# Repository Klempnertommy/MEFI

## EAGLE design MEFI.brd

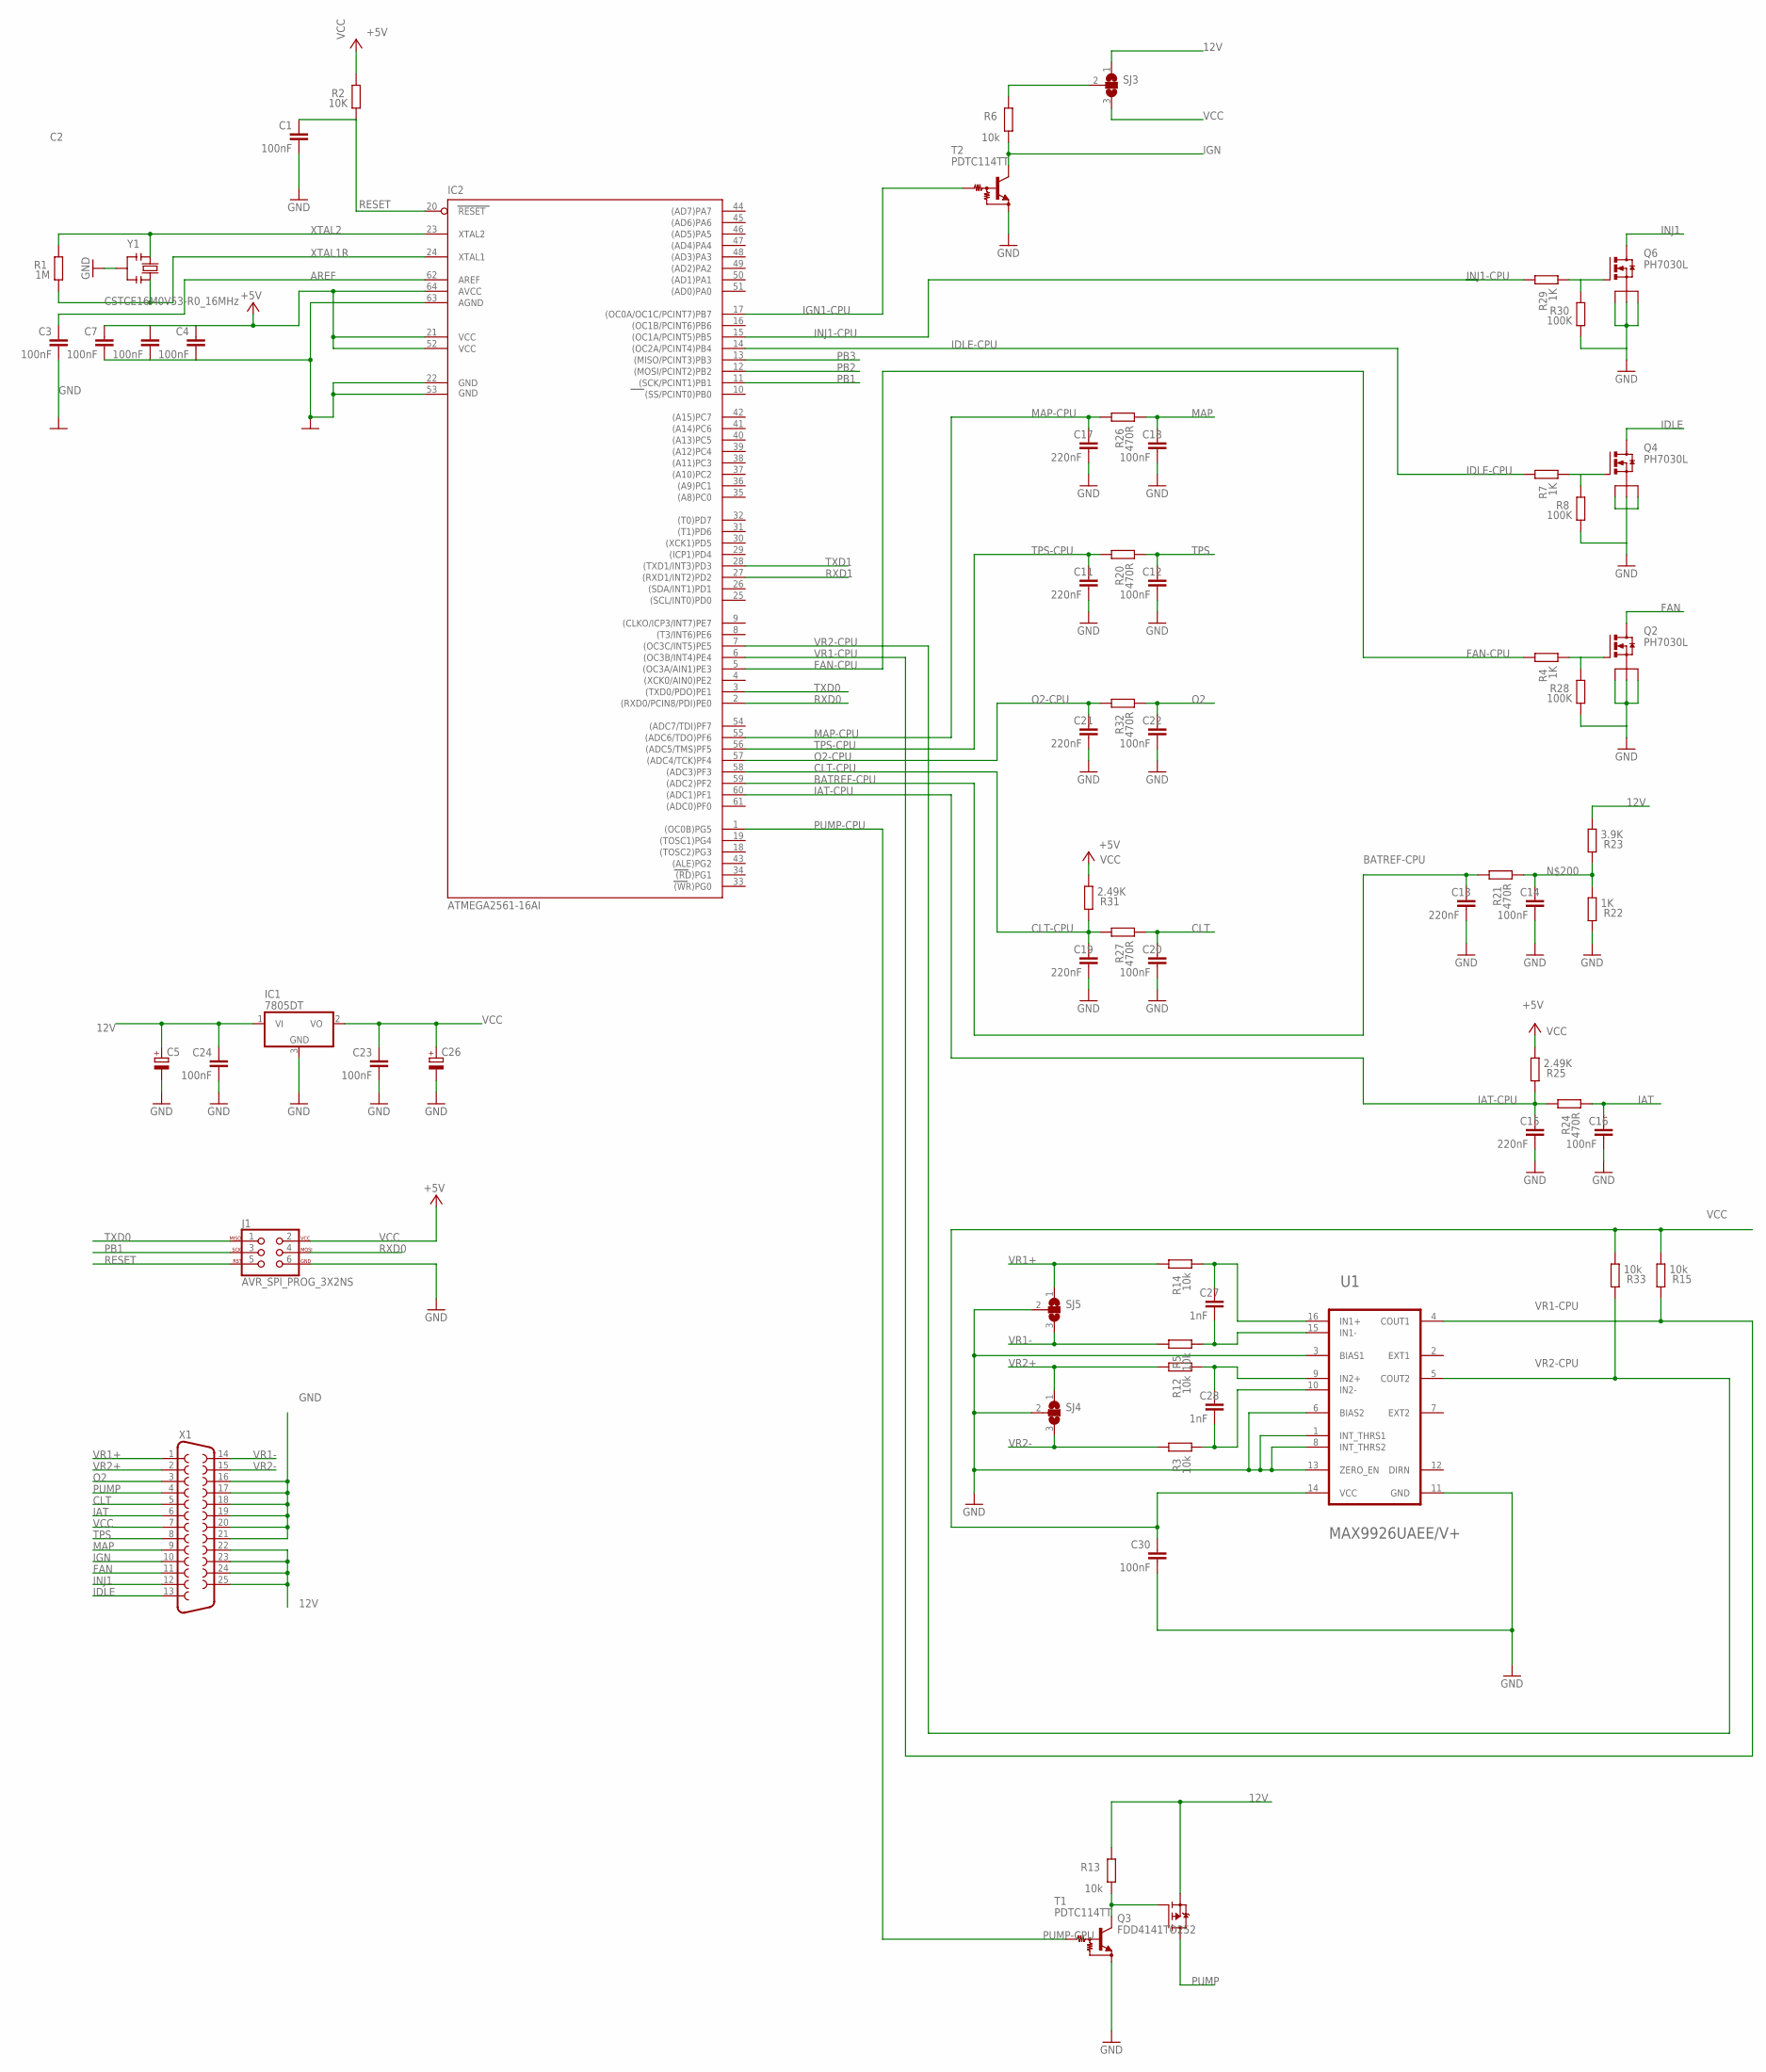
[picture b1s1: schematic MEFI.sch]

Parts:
C1, C2, C3, C4, C7, C12, C14, C16, C18, C20, C22, C23, C24, C30: 100nF; C0805
C5, C26: CPOL-EUTT2D7L; TT2D7L
C11, C13, C15, C17, C19, C21: 220nF; C0805
C27, C28: 1nF; C0805
IC1: 7805DT; TO252
IC2: ATMEGA2561-16AI; TQFP64
J1: AVR_SPI_PROG_3X2NS; 2X3-NS
Q2, Q4, Q6: PH7030L; SOT669
Q3: FDD4141TO252; TO252
R1: 1M; R0805
R2: 10K; R0805
R3, R5, R6, R12, R13, R14, R15, R33: 10k; R0805
R4, R7, R22, R29: 1K; R0805
R8, R28, R30: 100K; R0805
R20, R21, R24, R26, R27, R32: 470R; R0805
R23: 3.9K; R0805
R25, R31: 2.49K; R0805
SJ3, SJ4, SJ5: SJ2W; SJ_2
T1, T2: PDTC114TT; SC59-BEC
U1: MAXIM_MAX9926UAEE-V+MAXIM_MAX9926UAEE-V+_0_0; MAXIM_MAX9926UAEE-V+_0
X1: F25D
Y1: CSTCE16M0V53-R0_16MHz; RESONATOR

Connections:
12V: C5.+, C24.1, IC1.1 (VI), Q3.2 (S), R13.2, R23.1, SJ3.1, X1.22, X1.23, X1.24, X1.25
AREF: C3.1, IC2.62 (AREF)
BATREF-CPU: C13.1, IC2.59 ((ADC2)PF2), R21.2
CLT: C20.1, R27.1, X1.5
CLT-CPU: C19.1, IC2.58 ((ADC3)PF3), R27.2, R31.2
FAN: Q2.MB (D), X1.11
FAN-CPU: IC2.5 ((OC3A/AIN1)PE3), R4.2
GND: C1.2, C2.2, C3.2, C4.2, C5.-, C7.2, C11.2, C12.2, C13.2, C14.2, C15.2, C16.2, C17.2, C18.2, C19.2, C20.2, C21.2, C22.2, C23.2, C24.2, C26.-, C30.2, IC1.3 (GND), IC2.22 (GND), IC2.53 (GND1), IC2.63 (AGND), J1.6, Q2.1 (S), Q2.2 (S), Q2.3 (S), Q4.1 (S), Q4.2 (S), Q4.3 (S), Q6.1 (S), Q6.2 (S), Q6.3 (S), R8.1, R22.2, R28.1, R30.1, SJ4.2, SJ5.2, T1.E, T2.E, U1.1 (INT_THRS1), U1.3 (BIAS1), U1.6 (BIAS2), U1.8 (INT_THRS2), U1.11 (GND), U1.13 (ZERO_EN), X1.16, X1.17, X1.18, X1.19, X1.20, X1.21, Y1.2
IAT: C16.1, R24.1, X1.6
IAT-CPU: C15.1, IC2.60 ((ADC1)PF1), R24.2, R25.2
IDLE: Q4.MB (D), X1.13
IDLE-CPU: IC2.14 ((OC2A/PCINT4)PB4), R7.2
IGN: R6.1, T2.C, X1.10
IGN1-CPU: IC2.17 ((OC0A/OC1C/PCINT7)PB7), T2.B
INJ1: Q6.MB (D), X1.12
INJ1-CPU: IC2.15 ((OC1A/PCINT5)PB5), R29.2
MAP: C18.1, R26.1, X1.9
MAP-CPU: C17.1, IC2.55 ((ADC6/TDO)PF6), R26.2
unnamed: Q2.4 (G), R4.1, R28.2
unnamed: Q6.4 (G), R29.1, R30.2
unnamed: C28.2, R3.1, U1.10 (IN2-)
unnamed: C27.2, R5.1, U1.15 (IN1-)
unnamed: R6.2, SJ3.2
unnamed: Q3.1 (G), R13.1, T1.C
unnamed: C27.1, R14.1, U1.16 (IN1+)
unnamed: C28.1, R12.1, U1.9 (IN2+)
unnamed: Q4.4 (G), R7.1, R8.2
unnamed: C14.1, R21.1, R22.1, R23.2
O2: C22.1, R32.1, X1.3
O2-CPU: C21.1, IC2.57 ((ADC4/TCK)PF4), R32.2
PB1: IC2.11 ((SCK/PCINT1)PB1), J1.3
PB2: IC2.12 ((MOSI/PCINT2)PB2)
PB3: IC2.13 ((MISO/PCINT3)PB3)
PUMP: Q3.3 (D), X1.4
PUMP-CPU: IC2.1 ((OC0B)PG5), T1.B
RESET: C1.1, IC2.20 (RESET), J1.5, R2.1
RXD0: IC2.2 ((RXD0/PCIN8/PDI)PE0), J1.4
RXD1: IC2.27 ((RXD1/INT2)PD2)
TPS: C12.1, R20.1, X1.8
TPS-CPU: C11.1, IC2.56 ((ADC5/TMS)PF5), R20.2
TXD0: IC2.3 ((TXD0/PDO)PE1), J1.1
TXD1: IC2.28 ((TXD1/INT3)PD3)
VCC: C2.1, C4.1, C7.1, C23.1, C26.+, C30.1, IC1.2 (VO), IC2.21 (VCC), IC2.52 (VCC1), IC2.64 (AVCC), J1.2, R2.2, R15.1, R25.1, R31.1, R33.1, SJ3.3, U1.14 (VCC), X1.7
VR1+: R14.2, SJ5.1, X1.1
VR1-: R5.2, SJ5.3, X1.14
VR1-CPU: IC2.6 ((OC3B/INT4)PE4), R15.2, U1.4 (COUT1)
VR2+: R12.2, SJ4.1, X1.2
VR2-: R3.2, SJ4.3, X1.15
VR2-CPU: IC2.7 ((OC3C/INT5)PE5), R33.2, U1.5 (COUT2)
XTAL1R: IC2.24 (XTAL1), R1.1, Y1.3
XTAL2: IC2.23 (XTAL2), R1.2, Y1.1

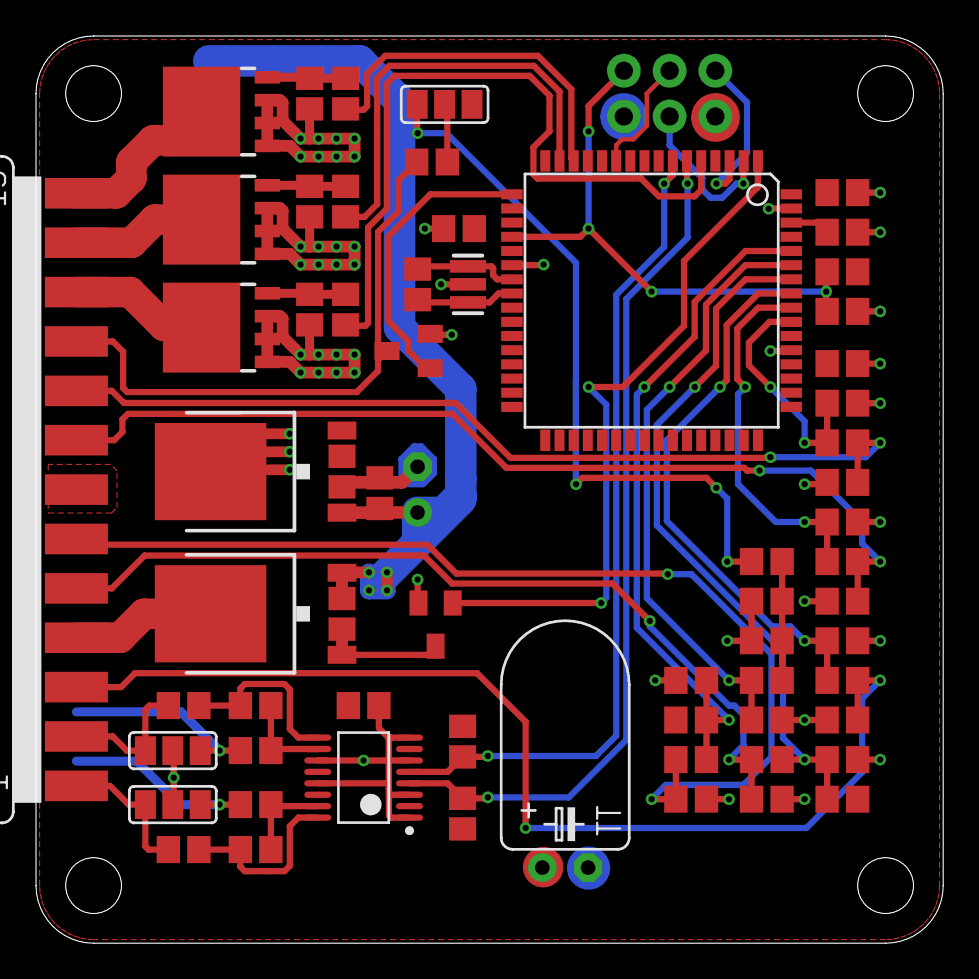
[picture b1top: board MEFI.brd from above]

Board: 2 copper layers, 50.4 x 50.4 mm, 65 parts (1 on the bottom side), 47 nets.

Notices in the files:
parts and their libraries:
SparkFun-Connectors: Licensing: Creative Commons ShareAlike 4.0 International - https://creativecommons.org/licenses/by-sa/4.0
